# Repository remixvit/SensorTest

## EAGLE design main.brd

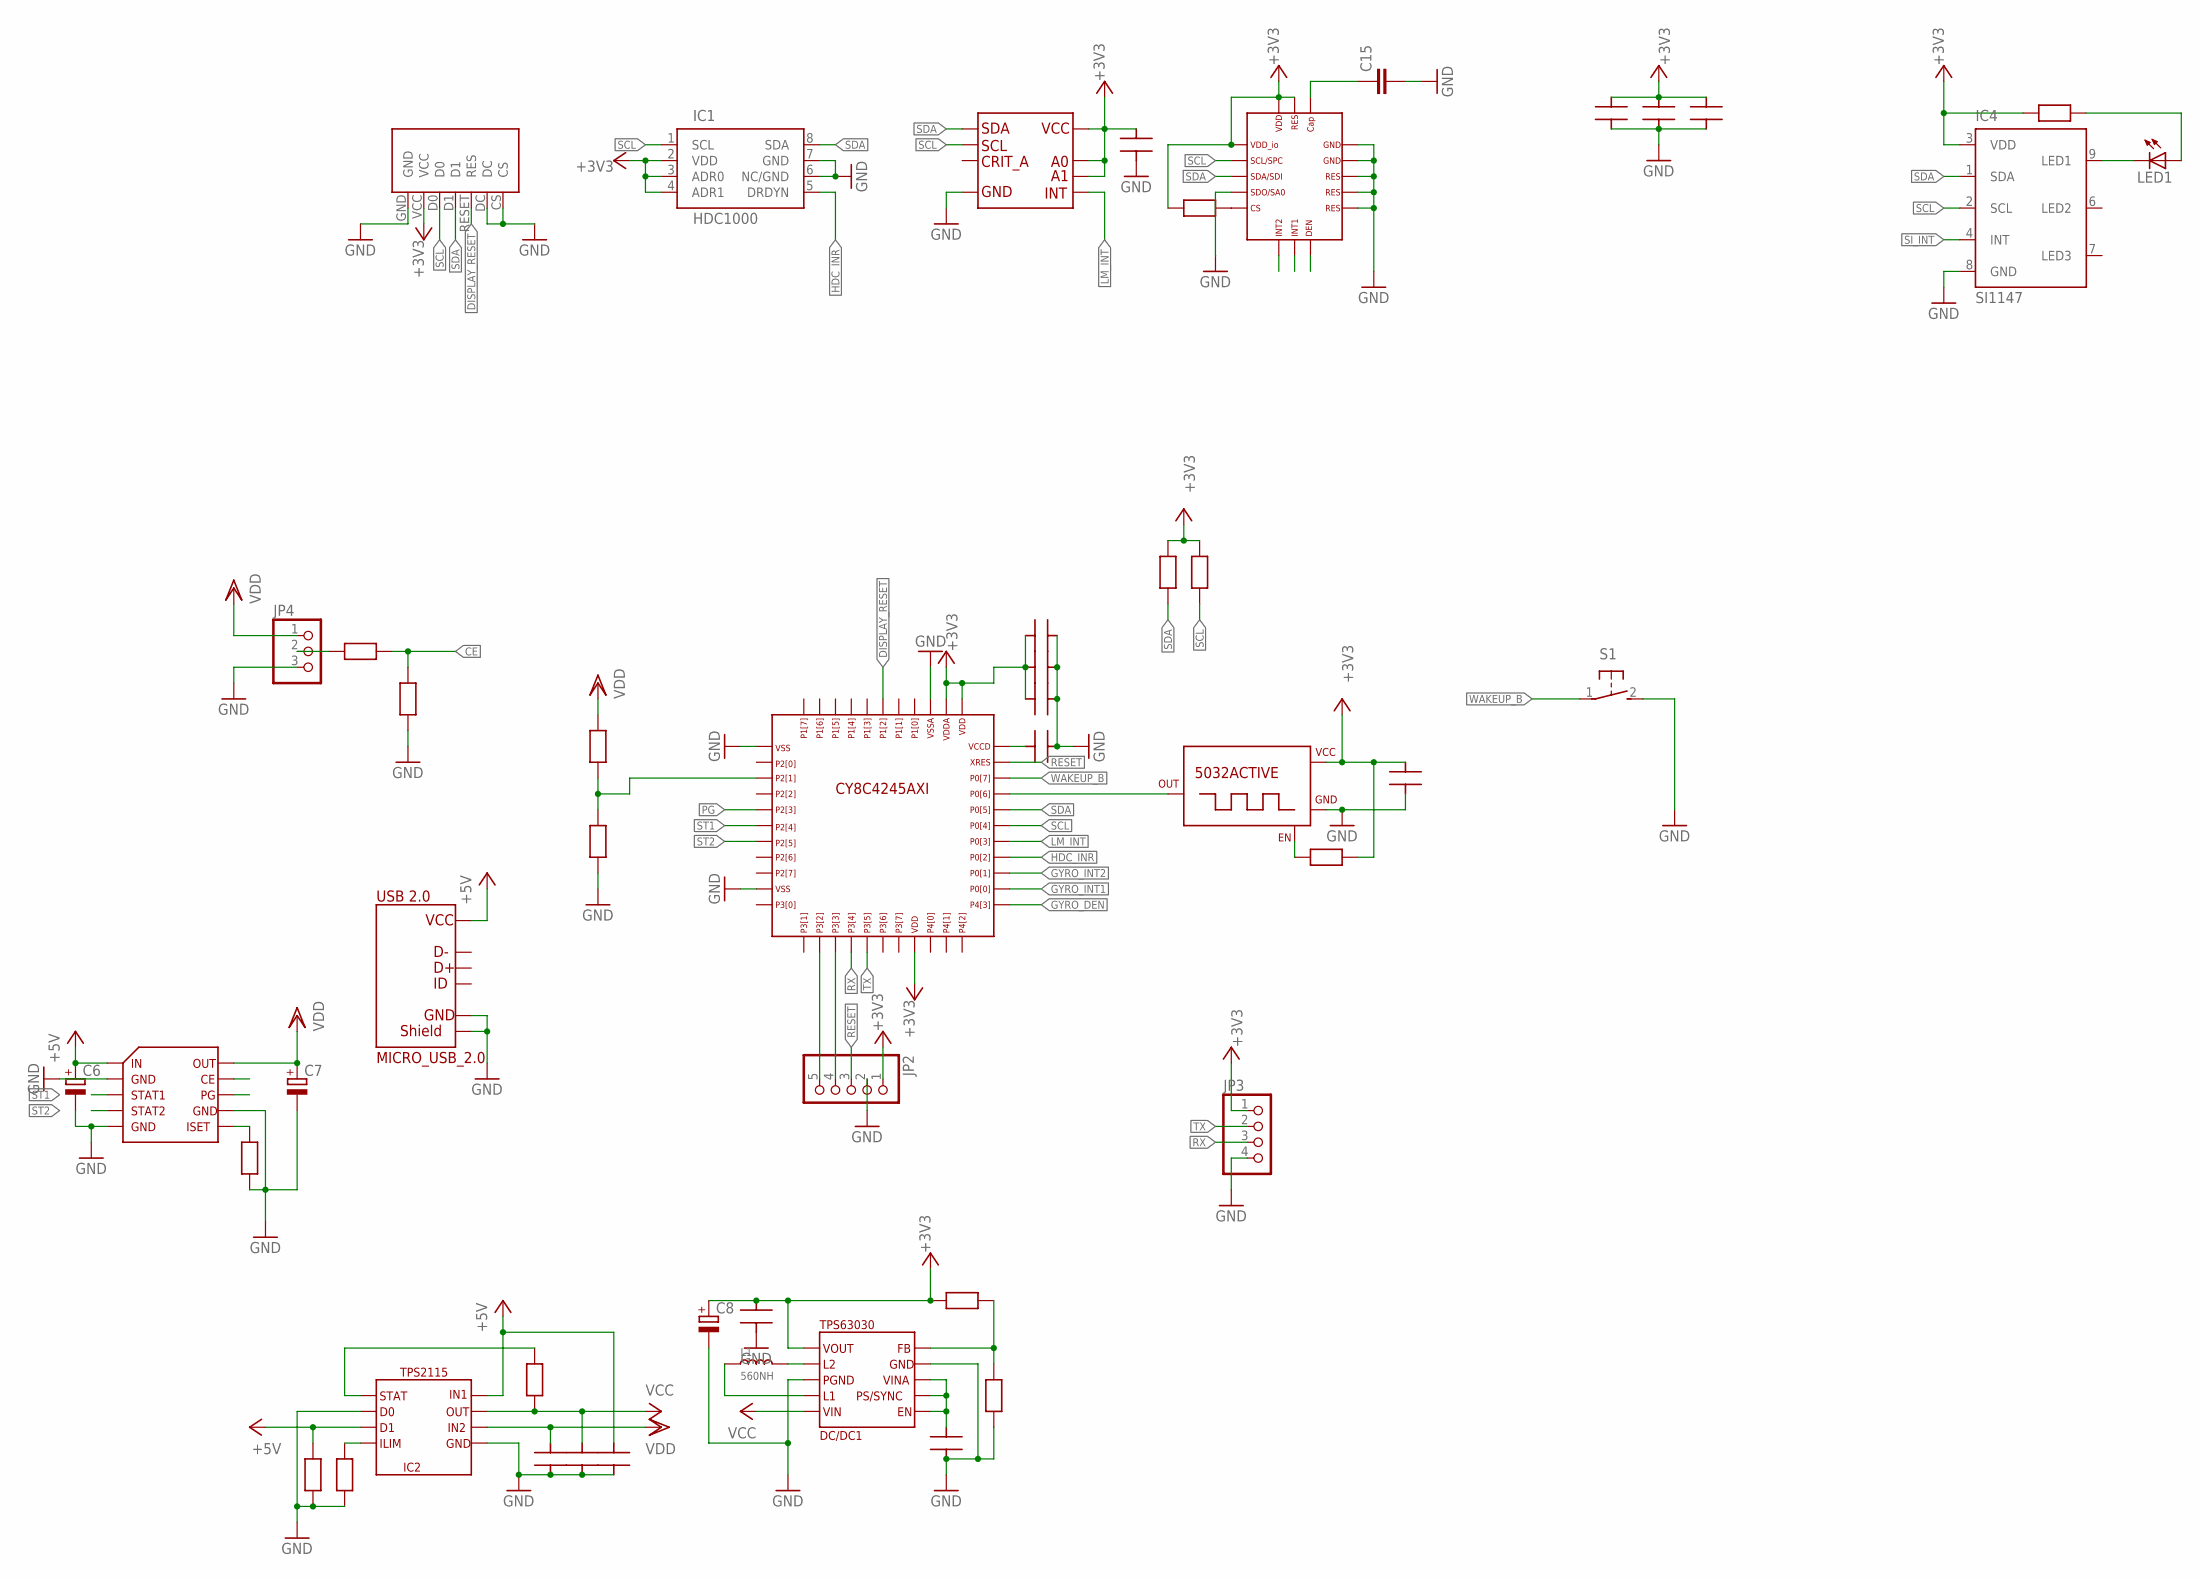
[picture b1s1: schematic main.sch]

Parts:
C1, C2, C3, C4, C5, C9, C10, C11, C12, C13, C14, C18, C19, C20: CAP0603; C0603
C6, C7, C8: CPOL-EUSMCA; SMC_A
C15: C-EUC1206; C1206
DC/DC1: TPS63030; WSON10
DIS1: ER-OLED_BREACKOUT; ER-OLED_BRECKOUT
GYRO1: L3GD20H; LGA_3X3_16
IC1: HDC1000; DSBGA-8
IC2: TPS2115; TSSOP8
IC3: BQ24080-Q1,; VSON10
IC4: SI1147; QFN-10
JP2: PINHD-1X5; 1X05
JP3: PINHD-1X4; 1X04
JP4: PINHD-1X3; 1X03
L1: 560NH; L0805
LED1: LED3MM
R1, R2, R3, R4, R5, R6, R7, R8, R9, R10, R11, R12, R13, R14, R15: RES0603; R0603
S1: 31-XX; B3F-31XX
TMP1: LM92; SOIC8-1.27-5X4MM
U$1: CY8C4245; TQFP44_CY_LOGO
U$2: 5032ACTIVE; 5030A
USB_CON1: MICRO_USB_2.0; MICRO-USB5+4P-SMD-0.65

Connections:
+3V3: C5.2, C8.+, C10.2, C11.2, C12.2, C13.1, C14.1, C18.1, C19.1, C20.1, DC/DC1.P$1, DIS1.VCC, GYRO1.1, GYRO1.15, GYRO1.16, IC1.2 (VDD), IC1.3 (ADR0), IC1.4 (ADR1), IC4.3 (VDD), JP2.1, JP3.1, R5.1, R9.2, R10.2, R11.1, R12.2, R13.2, TMP1.6, TMP1.7, TMP1.8, U$1.19, U$1.34, U$1.35, U$2.4 (+5V)
+5V: C3.2, C6.+, IC2.P$3, IC2.P$8, IC3.P$1, R2.2, USB_CON1.1
CE: IC3.P$9, R14.1, R15.1
DISPLAY_RESET: DIS1.RESET (RES), U$1.39
GND: C1.1, C2.1, C3.1, C4.1, C5.1, C6.-, C7.-, C8.-, C9.1, C10.1, C11.1, C12.1, C13.2, C14.2, C15.2, C18.2, C19.2, C20.2, DC/DC1.EPAD_B, DC/DC1.EPAD_T, DC/DC1.EPAD_VIA, DC/DC1.P$3, DC/DC1.P$9, DIS1.CS, DIS1.DC, DIS1.GND, GYRO1.4, GYRO1.9, GYRO1.10, GYRO1.11, GYRO1.12, GYRO1.13, IC1.6 (NC/GND), IC1.7 (GND), IC2.P$2, IC2.P$5, IC3.P$2, IC3.P$5, IC3.P$7, IC3.PAD1, IC3.PAD2, IC3.PAD3, IC3.PAD4, IC3.PAD5, IC4.8 (GND), JP2.2, JP3.4, JP4.3, R1.1, R2.1, R4.2, R6.1, R8.1, R15.2, S1.2 (S), TMP1.4, U$1.1, U$1.10, U$1.36, U$2.2 (GND), USB_CON1.5, USB_CON1.P$1, USB_CON1.P$2, USB_CON1.P$3, USB_CON1.P$4
GYRO_DEN: GYRO1.8, U$1.23
GYRO_INT1: GYRO1.7, U$1.24
GYRO_INT2: GYRO1.6, U$1.25
HDC_INR: IC1.5 (DRDYN), U$1.26
LM_INT: TMP1.5, U$1.27
unnamed: C4.2, DC/DC1.P$6, DC/DC1.P$7, DC/DC1.P$8
unnamed: DC/DC1.P$4, L1.1
unnamed: DC/DC1.P$2, L1.2
unnamed: DC/DC1.P$10, R4.1, R5.2
unnamed: IC2.P$4, R1.2
unnamed: C9.2, U$1.33
unnamed: IC2.P$1, R3.2
unnamed: IC3.P$6, R6.2
unnamed: JP2.5, U$1.13
unnamed: JP2.4, U$1.14
unnamed: R7.1, R8.2, U$1.3
unnamed: C15.1, GYRO1.14
unnamed: U$1.30, U$2.3 (OUT)
unnamed: R11.2, U$2.1 (EN)
unnamed: GYRO1.5, R12.1
unnamed: LED1.A, R13.1
unnamed: IC4.9 (LED1), LED1.K (C)
unnamed: JP4.2, R14.2
PG: IC3.P$8, U$1.5
RESET: JP2.3, U$1.32
RX: JP3.3, U$1.15
SCL: DIS1.D0, GYRO1.2, IC1.1 (SCL), IC4.2 (SCL), R10.1, TMP1.2, U$1.28
SDA: DIS1.D1, GYRO1.3, IC1.8 (SDA), IC4.1 (SDA), R9.1, TMP1.1, U$1.29
SI_INT: IC4.4 (INT)
ST1: IC3.P$3, U$1.6
ST2: IC3.P$4, U$1.7
TX: JP3.2, U$1.16
VCC: C2.2, DC/DC1.P$5, IC2.P$7, R3.1
VDD: C1.2, C7.+, IC2.P$6, IC3.P$10, JP4.1, R7.2
WAKEUP_B: S1.1, U$1.31

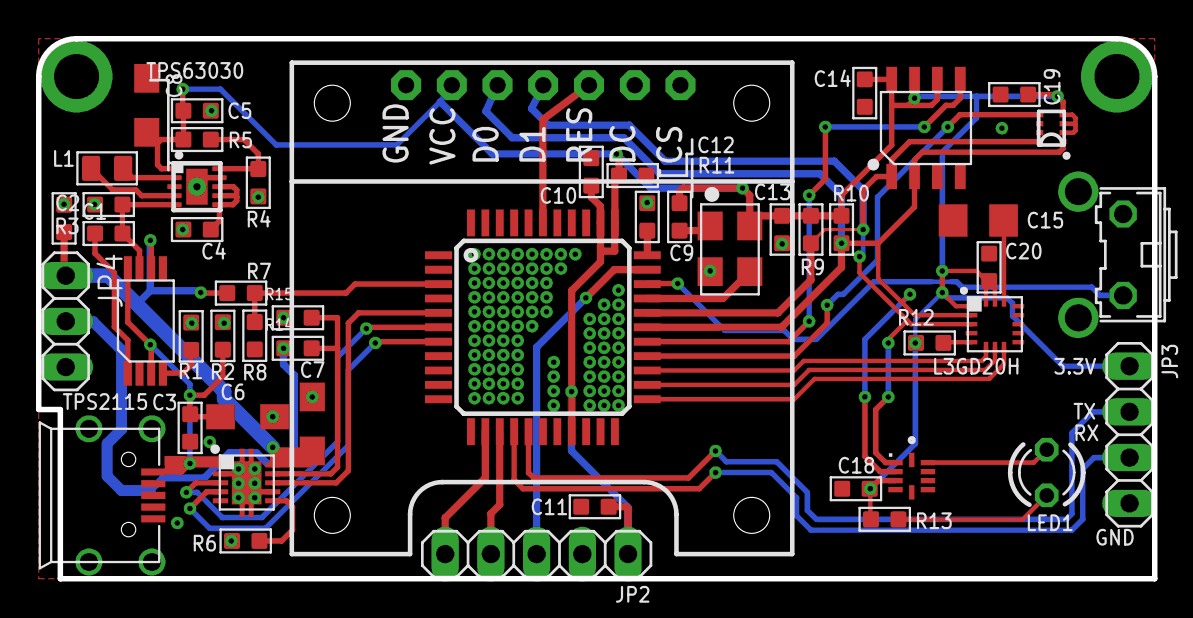
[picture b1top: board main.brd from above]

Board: 2 copper layers, 62.0 x 30.0 mm, 50 parts (0 on the bottom side), 39 nets.

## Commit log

2015-12-17 Create
2016-01-31 Create PSoc Project. Create ssd1306, LM92, Battery libs
2016-01-31 End PCB Routing
